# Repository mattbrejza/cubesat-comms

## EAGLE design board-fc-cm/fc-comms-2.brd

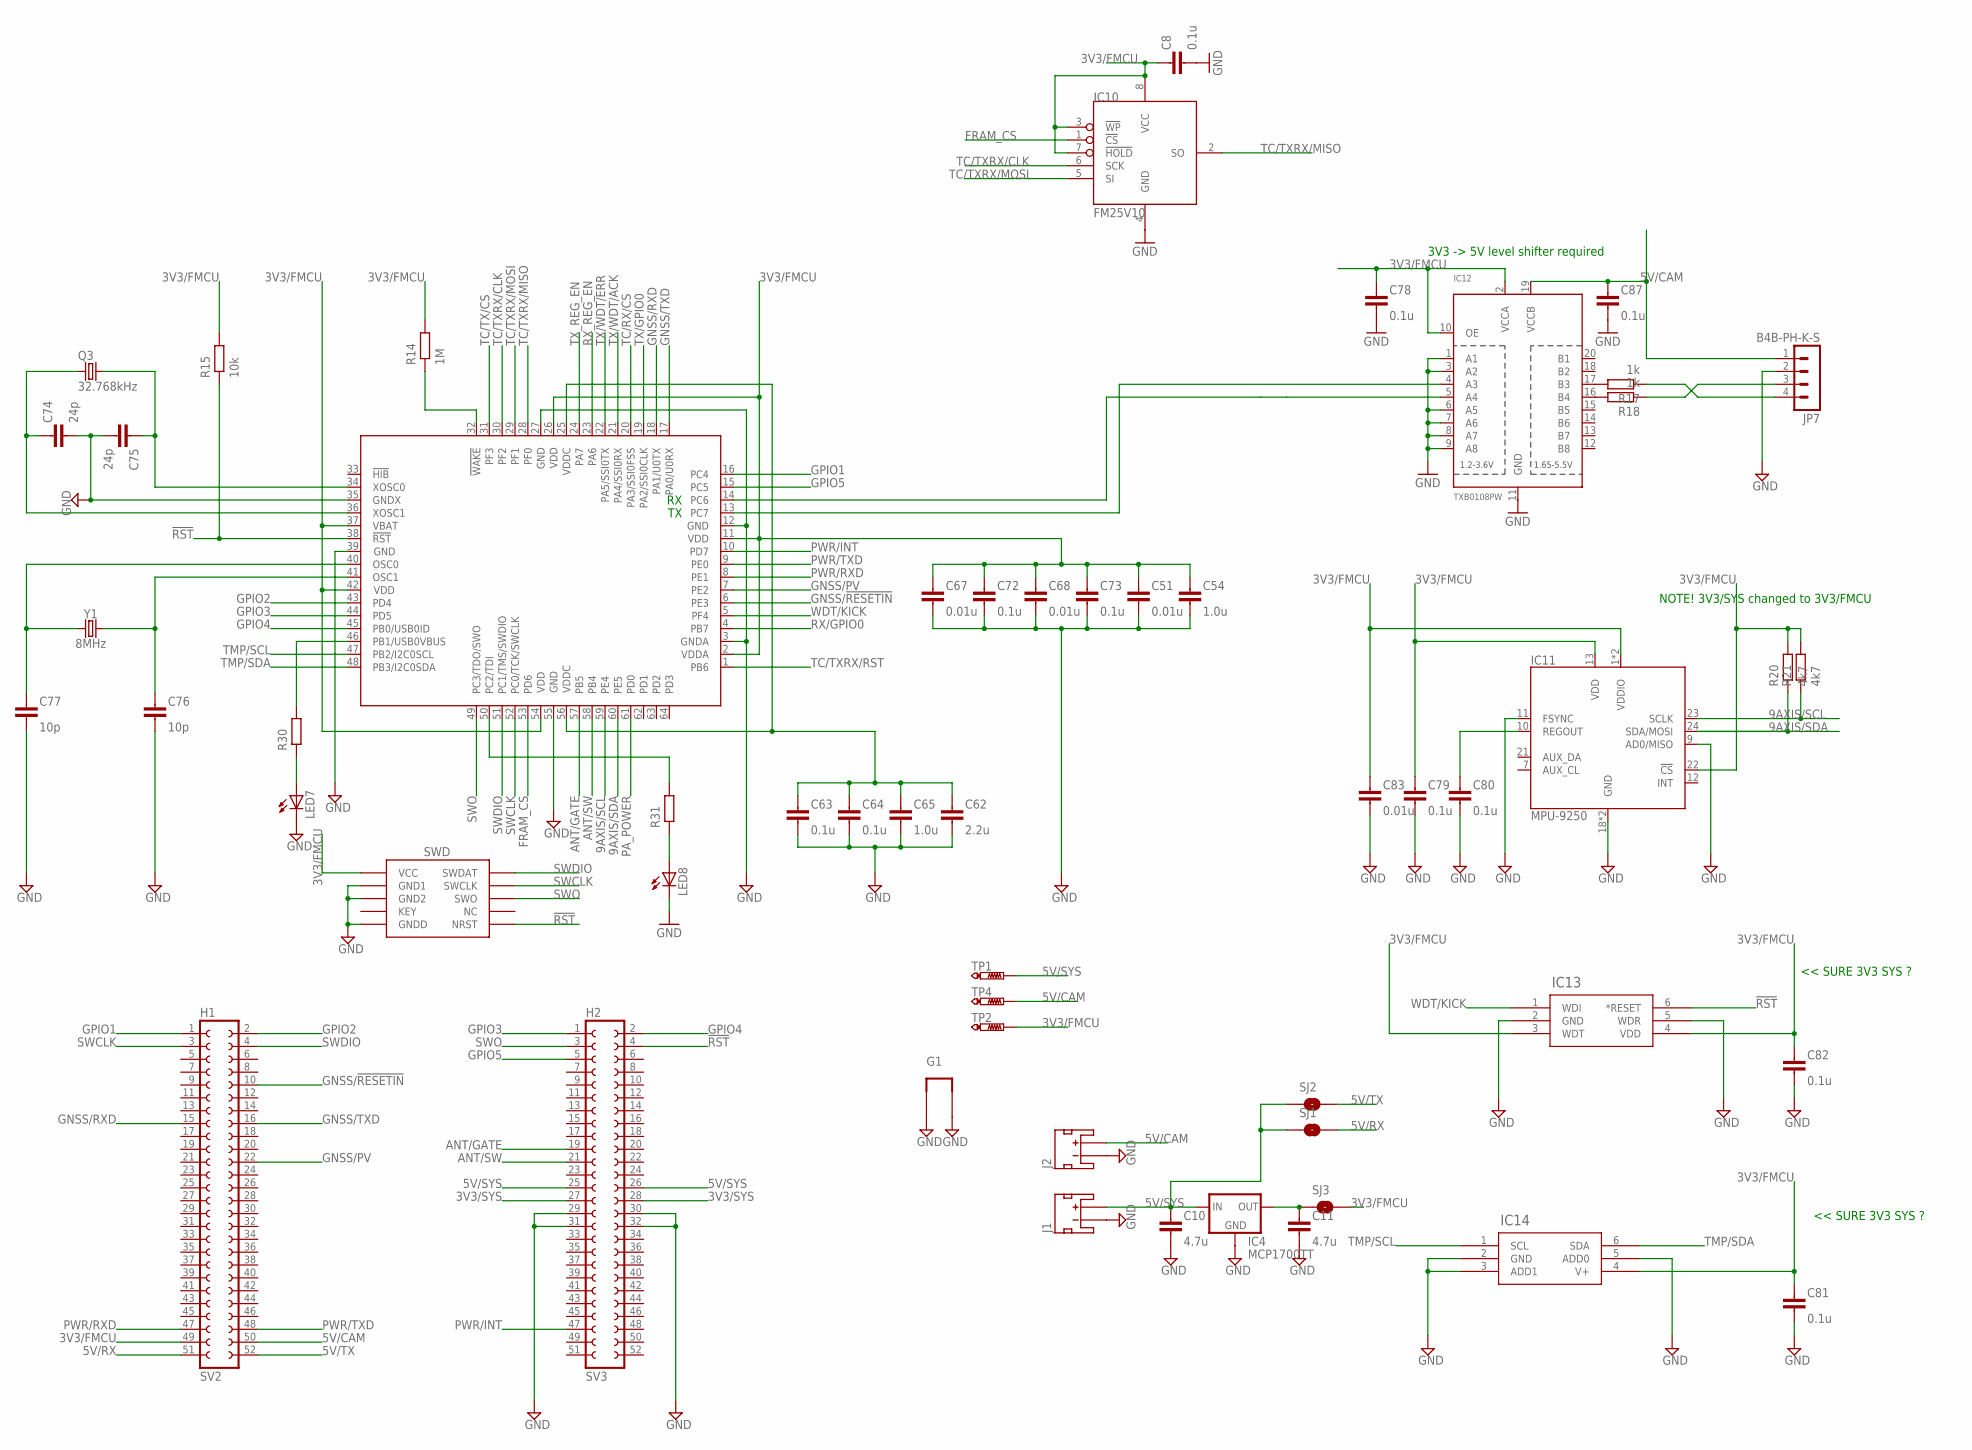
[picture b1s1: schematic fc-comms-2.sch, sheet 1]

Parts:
C8, C63, C64, C72, C73, C78, C79, C80, C81, C82, C87: 0.1u; C0603-N
C10, C11: 4.7u; C0603-N
C51, C67, C68, C83: 0.01u; C0603-N
C54, C65: 1.0u; C0603-N
C62: 2.2u; C0603-N
C74, C75: 24p; C0603-N
C76, C77: 10p; C0603-N
G1: GND-LOOPL; GND-LOOP-0.4
IC4: MCP1700TT; SOT23
IC9: TM4C123[7,G]XXPM; PM_S-PQFP-G64
IC10: FM25V10; SO-08M
IC11: MPU-9250; QFN-24/3MM
IC12: TXB0108PW; TSSOP20
IC13: TPS3813K33-EP_DBV_6; DBV6
IC14: TMP100-EP_DBV_6; DBV6
J1, J2: JST_2MM_MALE_TH; JST-2-TH
J3: SWD_SHROUD; SWD_PTH_SHROUD
JP7: B4B-PH-K-S
LED7, LED8: LEDCHIP-LED0603; CHIP-LED0603
Q3: 32.768kHz; RESONATOR_EPSON_FC_145; FARNELL 2101347
R14: 1M; R0603-N
R15: 10k; R0603-N
R17, R18: 1k; R0603-N
R20, R21: 4k7; R0603-N
R30, R31: RESISTOR0603-N; R0603-N
SJ1, SJ2, SJ3: JUMPER-PAD-2-NOYES_SILK; PAD-JUMPER-2-NO_YES_SILK
SV2: H1; FE26-2
SV3: H2; FE26-2
TP1, TP2, TP4: PTR1PAD1-13; P1-13
Y1: 8MHz; CRYSTAL-SMD-5X3.2-4PAD; FARNELL 2308726

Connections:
3V3/FMCU: C8.1, C51.1, C54.1, C67.1, C68.1, C72.1, C73.1, C78.1, C79.1, C81.1, C82.1, C83.1, IC9.2 (VDDA), IC9.11 (VDD), IC9.26 (VDD), IC9.37 (VBAT), IC9.42 (VDD), IC9.54 (VDD), IC10.3 (!WP), IC10.7 (!HOLD), IC10.8 (VCC), IC11.1 (VDDIO), IC11.8 (VDDIO), IC11.13 (VDD), IC11.22 (!CS), IC12.2 (VCCA), IC12.10 (OE), IC13.3 (WDT), IC13.4 (VDD), IC14.4 (V+), J3.1 (VCC), R14.2, R15.2, R20.2, R21.2, SJ3.2, SV2.49, TP2.TP; also elsewhere on the board
3V3/SYS: SV3.27, SV3.28
5V/CAM: C87.1, IC12.19 (VCCB), J2.1 (+), JP7.1, SV2.50, TP4.TP
5V/RX: SJ1.2, SV2.51; also elsewhere on the board
5V/SYS: C10.1, IC4.3 (IN), J1.1 (+), SJ1.1, SJ2.1, SV3.25, SV3.26, TP1.TP
5V/TX: SJ2.2, SV2.52; also elsewhere on the board
9AXIS/SCL: IC9.59 (PE4), IC11.23 (SCLK), R21.1
9AXIS/SDA: IC9.60 (PE5), IC11.24 (SDA/MOSI), R20.1
!RST: IC9.38 (!RST), IC13.6 (*RESET), J3.10 (NRST), R15.1, SV3.4
!WAKE: IC9.32 (!WAKE), R14.1
ANT/GATE: IC9.57 (PB5), SV3.19
ANT/SW: IC9.58 (PB4), SV3.21
CAM/RXD: IC9.13 (PC7), IC12.4 (A3)
CAM/TXD: IC9.14 (PC6), IC12.5 (A4)
FRAM_CS: IC9.53 (PD6), IC10.1 (!CS)
GND: C8.2, C10.2, C11.2, C51.2, C54.2, C62.2, C63.2, C64.2, C65.2, C67.2, C68.2, C72.2, C73.2, C74.2, C75.2, C76.2, C77.2, C78.2, C79.2, C80.2, C81.2, C82.2, C83.2, C87.2, G1.P$3 (1), G1.P$4 (2), IC4.1 (GND), IC9.3 (GNDA), IC9.12 (GND), IC9.27 (GND), IC9.35 (GNDX), IC9.39 (GND), IC9.55 (GND), IC10.4 (GND), IC11.9 (AD0/MISO), IC11.11 (FSYNC), IC11.18 (GND), IC11.20 (GND), IC12.1 (A1), IC12.3 (A2), IC12.6 (A5), IC12.7 (A6), IC12.8 (A7), IC12.9 (A8), IC12.11 (GND), IC13.2 (GND), IC13.5 (WDR), IC14.2 (GND), IC14.3 (ADD1), IC14.5 (ADD0), J1.2 (-), J2.2 (-), J3.3 (GND1), J3.5 (GND2), J3.9 (GNDD), JP7.2, LED7.C, LED8.C, SV3.29, SV3.30, SV3.31, SV3.32; also elsewhere on the board
GNSS/!RESETIN: IC9.6 (PE3), SV2.10
GNSS/PV: IC9.7 (PE2), SV2.22
GNSS/RXD: IC9.18 (PA1/U0TX), SV2.15
GNSS/TXD: IC9.17 (PA0/U0RX), SV2.16
GPIO1: IC9.16 (PC4), SV2.1
GPIO2: IC9.43 (PD4), SV2.2
GPIO3: IC9.44 (PD5), SV3.1
GPIO4: IC9.45 (PB0/USB0ID), SV3.2
GPIO5: IC9.15 (PC5), SV3.5
unnamed: C80.1, IC11.10 (REGOUT)
unnamed: C62.1, C63.1, C64.1, C65.1, IC9.25 (VDDC), IC9.56 (VDDC)
unnamed: C75.1, IC9.34 (XOSC0), Q3.P$2 (2)
unnamed: C77.1, IC9.40 (OSC0), Y1.1
unnamed: JP7.3, R18.1
unnamed: JP7.4, R17.1
unnamed: C76.1, IC9.41 (OSC1), Y1.3 (2)
unnamed: C74.1, IC9.36 (XOSC1), Q3.P$1 (1)
unnamed: LED7.A, R30.1
unnamed: LED8.A, R31.1
unnamed: IC9.50 (PC2/TDI), R31.2
unnamed: IC12.17 (B3), R17.2
unnamed: IC9.46 (PB1/USB0VBUS), R30.2
unnamed: IC12.16 (B4), R18.2
unnamed: C11.1, IC4.2 (OUT), SJ3.1
PA_POWER: IC9.61 (PD0); also elsewhere on the board
PWR/INT: IC9.10 (PD7), SV3.47
PWR/RXD: IC9.8 (PE1), SV2.47
PWR/TXD: IC9.9 (PE0), SV2.48
RX/GPIO0: IC9.4 (PB7); also elsewhere on the board
RX_REG_EN: IC9.23 (PA6); also elsewhere on the board
SWCLK: IC9.52 (PC0/TCK/SWCLK), J3.4 (SWCLK), SV2.3
SWDIO: IC9.51 (PC1/TMS/SWDIO), J3.2 (SWDAT), SV2.4
SWO: IC9.49 (PC3/TDO/SWO), J3.6 (SWO), SV3.3
TC/RX/CS: IC9.20 (PA3/SSI0FSS); also elsewhere on the board
TC/TX/CS: IC9.31 (PF3); also elsewhere on the board
TC/TXRX/CLK: IC9.30 (PF2), IC10.6 (SCK); also elsewhere on the board
TC/TXRX/MISO: IC9.28 (PF0), IC10.2 (SO); also elsewhere on the board
TC/TXRX/MOSI: IC9.29 (PF1), IC10.5 (SI); also elsewhere on the board
TC/TXRX/RST: IC9.1 (PB6); also elsewhere on the board
TMP/SCL: IC9.47 (PB2/I2C0SCL), IC14.1 (SCL); also elsewhere on the board
TMP/SDA: IC9.48 (PB3/I2C0SDA), IC14.6 (SDA); also elsewhere on the board
TX/GPIO0: IC9.19 (PA2/SSI0CLK); also elsewhere on the board
TX/WDT/ACK: IC9.21 (PA4/SSI0RX); also elsewhere on the board
TX/WDT/ERR: IC9.22 (PA5/SSI0TX); also elsewhere on the board
TX_REG_EN: IC9.24 (PA7); also elsewhere on the board
WDT/KICK: IC9.5 (PF4), IC13.1 (WDI)

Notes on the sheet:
3V3 -> 5V level shifter required
<< SURE 3V3 SYS ?
NOTE! 3V3/SYS changed to 3V3/FMCU

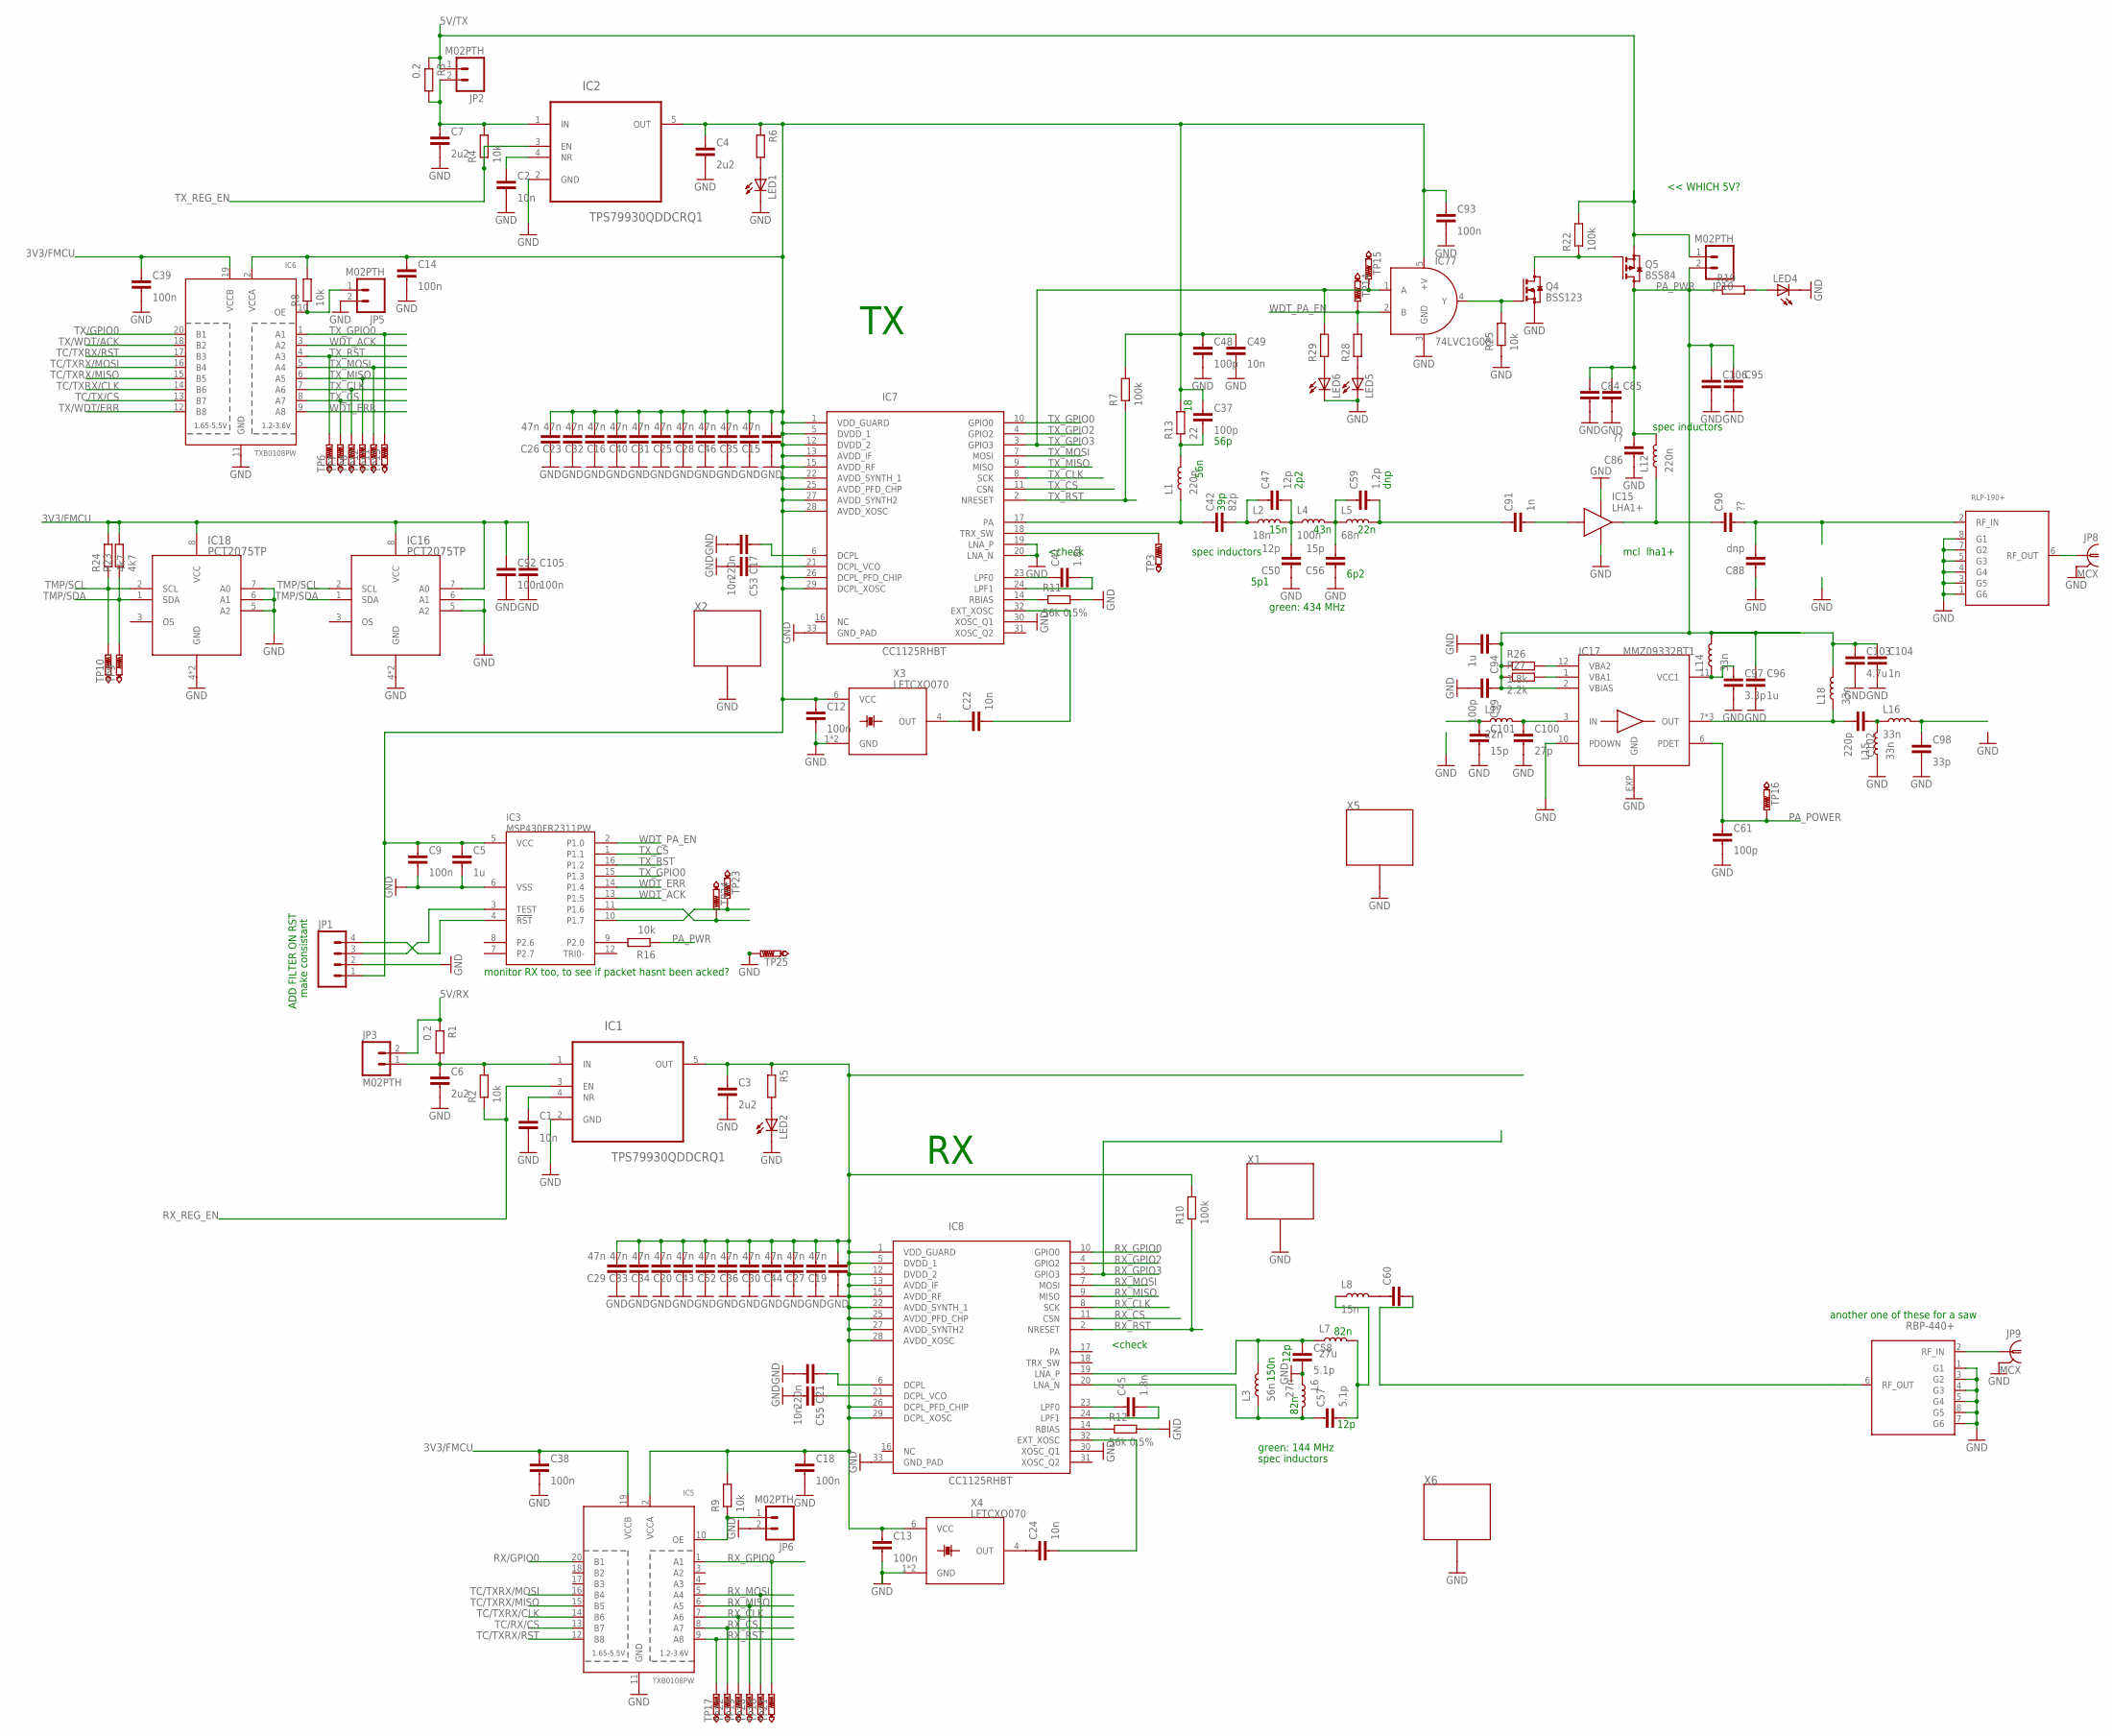
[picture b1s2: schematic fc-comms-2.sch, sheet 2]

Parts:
C1, C2, C22, C24, C49, C53, C55: 10n; C0603-N
C3, C4, C6, C7: 2u2; C0603-N
C5, C94, C96: 1u; C0603-N
C9, C12, C13, C14, C18, C38, C39, C92, C93, C105: 100n; C0603-N
C15, C16, C19, C20, C23, C25, C26, C27, C28, C29, C30, C31, C32, C33, C34, C35, C36, C40, C43, C44, C46, C52: 47n; C0603-N
C17, C21: 220n; C0603-N
C37, C48, C61, C99: 100p; C0603-N
C41, C45: 1.8n; C0603-N
C42: 82p; C0603-N
C47, C50: 12p; C0603-N
C56, C101: 15p; C0603-N
C57, C58: 5.1p; C0603-N
C59: 1.2p; C0603-N
C60: CAPACITOR0603-N; C0603-N
C84, C85, C95, C106: CAPACITOR0805-N; C0805-N
C86, C90: ??; C0603-N
C88: dnp; C0603-N
C91, C104: 1n; C0603-N
C97: 3.3p; C0603-N
C98: 33p; C0603-N
C100: 27p; C0603-N
C102: 220p; C0603-N
C103: 4.7u; C0603-N
FL2: SAW_FILTER_CS; PL-176
FL3: LPF_CS; PL-176
IC1, IC2: TPS79930QDDCRQ1; SOT95P280X110-5N
IC3: MSP430FR2311PW; SSOP16
IC5, IC6: TXB0108PW; TSSOP20
IC7, IC8: CC1125RHBT; QFN32_5X5
IC15: LHA1+; PA
IC16, IC18: PCT2075TP; HWSON8
IC17: MMZ09332BT1; QFN3X3-6
IC77: 74LVC1G08; SOT23-5
JP1: M04PTH; 1X04
JP2, JP3, JP5, JP6, JP10: M02PTH; 1X02
JP8, JP9: MCX; MCX-STRAIGHT
L1, L12: 220n; L0603-N
L2: 18n; L0603-N
L3: 56n; L0603-N
L4: 100n; L0603-N
L5: 68n; L0603-N
L6: 27n; L0603-N
L7: 27u; L0603-N
L8: 15n; L0603-N
L14, L15, L16, L18: 33n; L0603-N
L17: 22n; L0603-N
LED1, LED2, LED4, LED5, LED6: LEDCHIP-LED0603; CHIP-LED0603
Q4: BSS123; SOT23
Q5: BSS84; SOT23
R1, R3: 0.2; R0603-N
R2, R4, R8, R9, R16, R25: 10k; R0603-N
R5, R6, R19, R28, R29: RESISTOR0603-N; R0603-N
R7, R10, R22: 100k; R0603-N
R11, R12: 56k 0.5%; R0603-N
R13: 22; R0603-N
R23, R24: 4k7; R0603-N
R26: 1.8k; R0603-N
R27: 2.2k; R0603-N
TP3, TP6, TP7, TP8, TP9, TP10, TP11, TP12, TP13, TP14, TP15, TP16, TP17, TP18, TP19, TP20, TP21, TP22, TP23, TP24, TP25: PTR1B1,27; B1,27
X1, X2, X5, X6: SHIELD-26X26
X3, X4: LFTCXO070; 260-SERIES

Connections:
3V3/FMCU: C38.1, C39.1, C92.1, C105.1, IC5.19 (VCCB), IC6.19 (VCCB), IC16.7 (A0), IC16.8 (VCC), IC18.8 (VCC), R23.2, R24.2; also elsewhere on the board
5V/RX: JP3.2, R1.1; also elsewhere on the board
5V/TX: JP2.1, JP10.1, Q5.2 (S), R3.1, R22.2; also elsewhere on the board
EWFEWF: C6.1, IC1.1 (IN), JP3.1, R1.2, R2.2
GND: C1.2, C2.2, C3.2, C4.2, C5.2, C6.2, C7.2, C9.2, C12.2, C13.2, C14.2, C15.1, C16.1, C17.2, C18.2, C19.1, C20.1, C21.2, C23.1, C25.1, C26.1, C27.1, C28.1, C29.1, C30.1, C31.1, C32.1, C33.1, C34.1, C35.1, C36.1, C38.2, C39.2, C40.1, C43.1, C44.1, C46.1, C48.2, C49.2, C50.1, C52.1, C53.2, C55.2, C56.1, C58.2, C61.2, C84.2, C85.2, C86.1, C88.1, C92.2, C93.2, C94.2, C95.2, C96.2, C97.2, C98.2, C99.2, C100.2, C101.2, C103.2, C104.2, C105.2, C106.2, FL2.1 (G1), FL2.3 (G2), FL2.4 (G3), FL2.5 (G4), FL2.7 (G6), FL2.8 (G5), FL3.1 (G6), FL3.3 (G5), FL3.4 (G4), FL3.5 (G3), FL3.7 (G2), FL3.8 (G1), IC1.2 (GND), IC2.2 (GND), IC3.6 (VSS), IC5.11 (GND), IC6.11 (GND), IC7.19 (LNA_P), IC7.20 (LNA_N), IC7.30 (XOSC_Q1), IC7.33 (GND_PAD), IC8.30 (XOSC_Q1), IC8.33 (GND_PAD), IC15.GND1, IC15.GND2, IC16.4 (GND), IC16.5 (A2), IC16.6 (A1), IC16.EP (GND), IC17.10 (PDOWN), IC17.EXP (GND), IC18.4 (GND), IC18.5 (A2), IC18.6 (A1), IC18.7 (A0), IC18.EP (GND), IC77.3 (GND), JP1.2, JP5.2, JP6.2, JP8.P$2 (2), JP8.P$3 (2), JP8.P$4 (2), JP8.P$5 (2), JP9.P$2 (2), JP9.P$3 (2), JP9.P$4 (2), JP9.P$5 (2), L6.1, L15.1, LED1.C, LED2.C, LED4.C, LED5.C, LED6.C, Q4.2 (S), R11.2, R12.2, R25.1, TP25.TP, X1.G1, X1.G2, X1.G3, X1.G4, X1.G5, X1.G6, X1.G7, X1.G8, X1.G9, X1.G10, X1.G11, X1.G12, X1.G13, X1.G14, X1.G15, X1.G16, X1.G17, X1.G19, X1.G20, X1.G21, X2.G1, X2.G2, X2.G3, X2.G4, X2.G5, X2.G6, X2.G7, X2.G8, X2.G9, X2.G10, X2.G11, X2.G12, X2.G13, X2.G14, X2.G15, X2.G16, X2.G17, X2.G19, X2.G20, X2.G21, X3.1 (GND), X3.3 (GND), X4.1 (GND), X4.3 (GND), X5.G1, X5.G2, X5.G3, X5.G4, X5.G5, X5.G6, X5.G7, X5.G8, X5.G9, X5.G10, X5.G11, X5.G12, X5.G13, X5.G14, X5.G15, X5.G16, X5.G17, X5.G19, X5.G20, X5.G21, X6.G1, X6.G2, X6.G3, X6.G4, X6.G5, X6.G6, X6.G7, X6.G8, X6.G9, X6.G10, X6.G11, X6.G12, X6.G13, X6.G14, X6.G15, X6.G16, X6.G17, X6.G19, X6.G20, X6.G21; also elsewhere on the board
unnamed: IC3.9 (P2.0), R16.2
unnamed: C41.1, IC7.23 (LPF0)
unnamed: C41.2, IC7.24 (LPF1)
unnamed: LED5.A, R28.1
unnamed: C53.1, IC7.21 (DCPL_VCO)
unnamed: C42.1, IC7.17 (PA), L1.1
unnamed: IC7.14 (RBIAS), R11.1
unnamed: C22.2, IC7.32 (EXT_XOSC)
unnamed: C37.2, L1.2, R13.1
unnamed: C91.2, IC15.RF_IN
unnamed: C90.1, IC15.RF_OUT, L12.1
unnamed: C17.1, IC7.6 (DCPL)
unnamed: C42.2, C47.1, L2.1
unnamed: C47.2, C50.2, L2.2, L4.1
unnamed: C56.2, C59.1, L4.2, L5.1
unnamed: C59.2, C91.1, L5.2
unnamed: LED6.A, R29.1
unnamed: C88.2, C90.2, FL3.2 (RF_IN)
unnamed: FL3.6 (RF_OUT), JP8.P$1 (1)
unnamed: C45.1, IC8.23 (LPF0)
unnamed: C45.2, IC8.24 (LPF1)
unnamed: C55.1, IC8.21 (DCPL_VCO)
unnamed: IC8.14 (RBIAS), R12.1
unnamed: C24.2, IC8.32 (EXT_XOSC)
unnamed: LED4.A, R19.2
unnamed: IC7.18 (TRX_SW), TP3.TP
unnamed: C4.1, C5.1, C9.1, C12.1, C14.1, C15.2, C16.2, C23.2, C25.2, C26.2, C28.2, C31.2, C32.2, C35.2, C37.1, C40.2, C46.2, C48.1, C49.1, C93.1, IC2.5 (OUT), IC3.5 (VCC), IC6.2 (VCCA), IC7.1 (VDD_GUARD), IC7.5 (DVDD_1), IC7.12 (DVDD_2), IC7.13 (AVDD_IF), IC7.15 (AVDD_RF), IC7.22 (AVDD_SYNTH_1), IC7.25 (AVDD_PFD_CHP), IC7.26 (DCPL_PFD_CHIP), IC7.27 (AVDD_SYNTH2), IC7.28 (AVDD_XOSC), IC7.29 (DCPL_XOSC), IC77.5 (+V), JP1.1, R6.1, R7.2, R8.2, R13.2, X3.6 (VCC)
unnamed: LED1.A, R6.2
unnamed: C21.1, IC8.6 (DCPL)
unnamed: LED2.A, R5.2
unnamed: C58.1, IC8.19 (LNA_P), L3.2, L7.1
unnamed: C57.1, IC8.20 (LNA_N), L3.1, L6.2
unnamed: C3.1, C13.1, C18.1, C19.2, C20.2, C27.2, C29.2, C30.2, C33.2, C34.2, C36.2, C43.2, C44.2, C52.2, IC1.5 (OUT), IC5.2 (VCCA), IC8.1 (VDD_GUARD), IC8.5 (DVDD_1), IC8.12 (DVDD_2), IC8.13 (AVDD_IF), IC8.15 (AVDD_RF), IC8.22 (AVDD_SYNTH_1), IC8.25 (AVDD_PFD_CHP), IC8.26 (DCPL_PFD_CHIP), IC8.27 (AVDD_SYNTH2), IC8.28 (AVDD_XOSC), IC8.29 (DCPL_XOSC), R5.1, R9.2, R10.2, X4.6 (VCC)
unnamed: FL2.2 (RF_IN), JP9.P$1 (1)
unnamed: C60.2, FL2.6 (RF_OUT)
unnamed: C2.1, IC2.4 (NR)
unnamed: C1.1, IC1.4 (NR)
unnamed: Q4.3 (D), Q5.1 (G), R22.1
unnamed: C102.1, L15.2, L16.1
unnamed: C102.2, IC17.7 (OUT), IC17.8 (OUT), IC17.9 (OUT), L18.1
unnamed: C98.1, L16.2
unnamed: C97.1, IC17.11 (VCC1), L14.1
unnamed: IC17.12 (VBA2), R26.2
unnamed: IC17.1 (VBA1), R27.2
unnamed: C101.1, L17.1
unnamed: C100.1, IC17.3 (IN), L17.2
unnamed: C22.1, X3.4 (OUT)
unnamed: C24.1, X4.4 (OUT)
unnamed: IC3.3 (TEST), JP1.3
unnamed: IC3.4 (!RST), JP1.4
unnamed: IC3.11 (P1.6), TP24.TP
unnamed: IC3.10 (P1.7), TP23.TP
unnamed: C60.1, L8.2
unnamed: C57.2, L7.2, L8.1
unnamed: IC6.10 (OE), JP5.1, R8.1
unnamed: IC5.10 (OE), JP6.1, R9.1
unnamed: C7.1, IC2.1 (IN), JP2.2, R3.2, R4.2
unnamed: IC77.4 (Y), Q4.1 (G), R25.2
PA_POWER: C61.1, IC17.6 (PDET), TP16.TP; also elsewhere on the board
PA_PWR: C84.1, C85.1, C86.2, C94.1, C95.1, C96.1, C99.1, C103.1, C104.1, C106.1, IC17.2 (VBIAS), JP10.2, L12.2, L14.2, L18.2, Q5.3 (D), R16.1, R19.1, R26.1, R27.1
RX/GPIO0: IC5.20 (B1); also elsewhere on the board
RX_CLK: IC5.7 (A6), IC8.8 (SCK), TP19.TP
RX_CS: IC5.8 (A7), IC8.11 (CSN), TP22.TP
RX_GPIO0: IC5.1 (A1), IC8.10 (GPIO0), TP21.TP
RX_GPIO2: IC8.4 (GPIO2)
RX_GPIO3: IC8.3 (GPIO3)
RX_MISO: IC5.6 (A5), IC8.9 (MISO), TP20.TP
RX_MOSI: IC5.5 (A4), IC8.7 (MOSI), TP18.TP
RX_REG_EN: IC1.3 (EN), R2.1; also elsewhere on the board
RX_RST: IC5.9 (A8), IC8.2 (NRESET), R10.1, TP17.TP
TC/RX/CS: IC5.13 (B7); also elsewhere on the board
TC/TX/CS: IC6.13 (B7); also elsewhere on the board
TC/TXRX/CLK: IC5.14 (B6), IC6.14 (B6); also elsewhere on the board
TC/TXRX/MISO: IC5.15 (B5), IC6.15 (B5); also elsewhere on the board
TC/TXRX/MOSI: IC5.16 (B4), IC6.16 (B4); also elsewhere on the board
TC/TXRX/RST: IC5.12 (B8), IC6.17 (B3); also elsewhere on the board
TMP/SCL: IC16.2 (SCL), IC18.2 (SCL), R24.1, TP10.TP; also elsewhere on the board
TMP/SDA: IC16.1 (SDA), IC18.1 (SDA), R23.1, TP9.TP; also elsewhere on the board
TX/GPIO0: IC6.20 (B1); also elsewhere on the board
TX/WDT/ACK: IC6.18 (B2); also elsewhere on the board
TX/WDT/ERR: IC6.12 (B8); also elsewhere on the board
TX_CLK: IC6.7 (A6), IC7.8 (SCK), TP8.TP
TX_CS: IC3.1 (P1.1), IC6.8 (A7), IC7.11 (CSN), TP7.TP
TX_GPIO0: IC3.15 (P1.3), IC6.1 (A1), IC7.10 (GPIO0), TP13.TP
TX_GPIO2: IC7.4 (GPIO2)
TX_GPIO3: IC7.3 (GPIO3), IC77.1 (A), R29.2, TP15.TP
TX_MISO: IC6.6 (A5), IC7.9 (MISO), TP12.TP
TX_MOSI: IC6.5 (A4), IC7.7 (MOSI), TP11.TP
TX_REG_EN: IC2.3 (EN), R4.1; also elsewhere on the board
TX_RST: IC3.16 (P1.2), IC6.4 (A3), IC7.2 (NRESET), R7.1, TP6.TP
WDT_ACK: IC3.13 (P1.5), IC6.3 (A2)
WDT_ERR: IC3.14 (P1.4), IC6.9 (A8)
WDT_PA_EN: IC3.2 (P1.0), IC77.2 (B), R28.2, TP14.TP

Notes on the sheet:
spec inductors
<check
another one of these for a saw
mcl lha1+
make consistant
5p1
150n
82n
12p
green: 144 MHz
56n
56p
39p
2p2
6p2
15n
43n
22n
dnp
green: 434 MHz
monitor RX too, to see if packet hasnt been acked?
<< WHICH 5V?
ADD FILTER ON RST

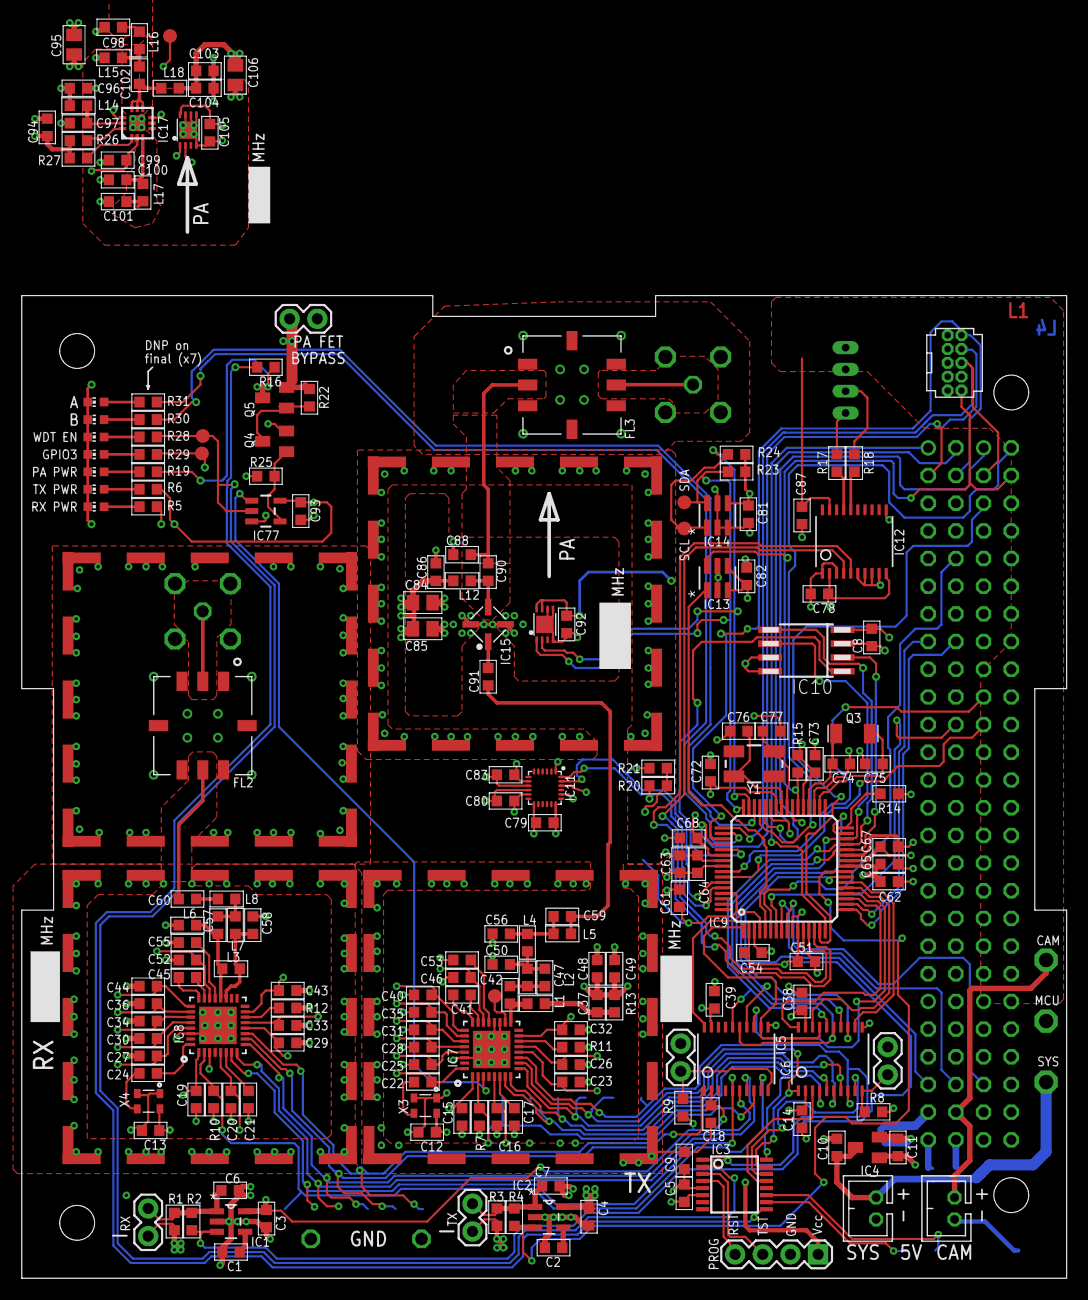
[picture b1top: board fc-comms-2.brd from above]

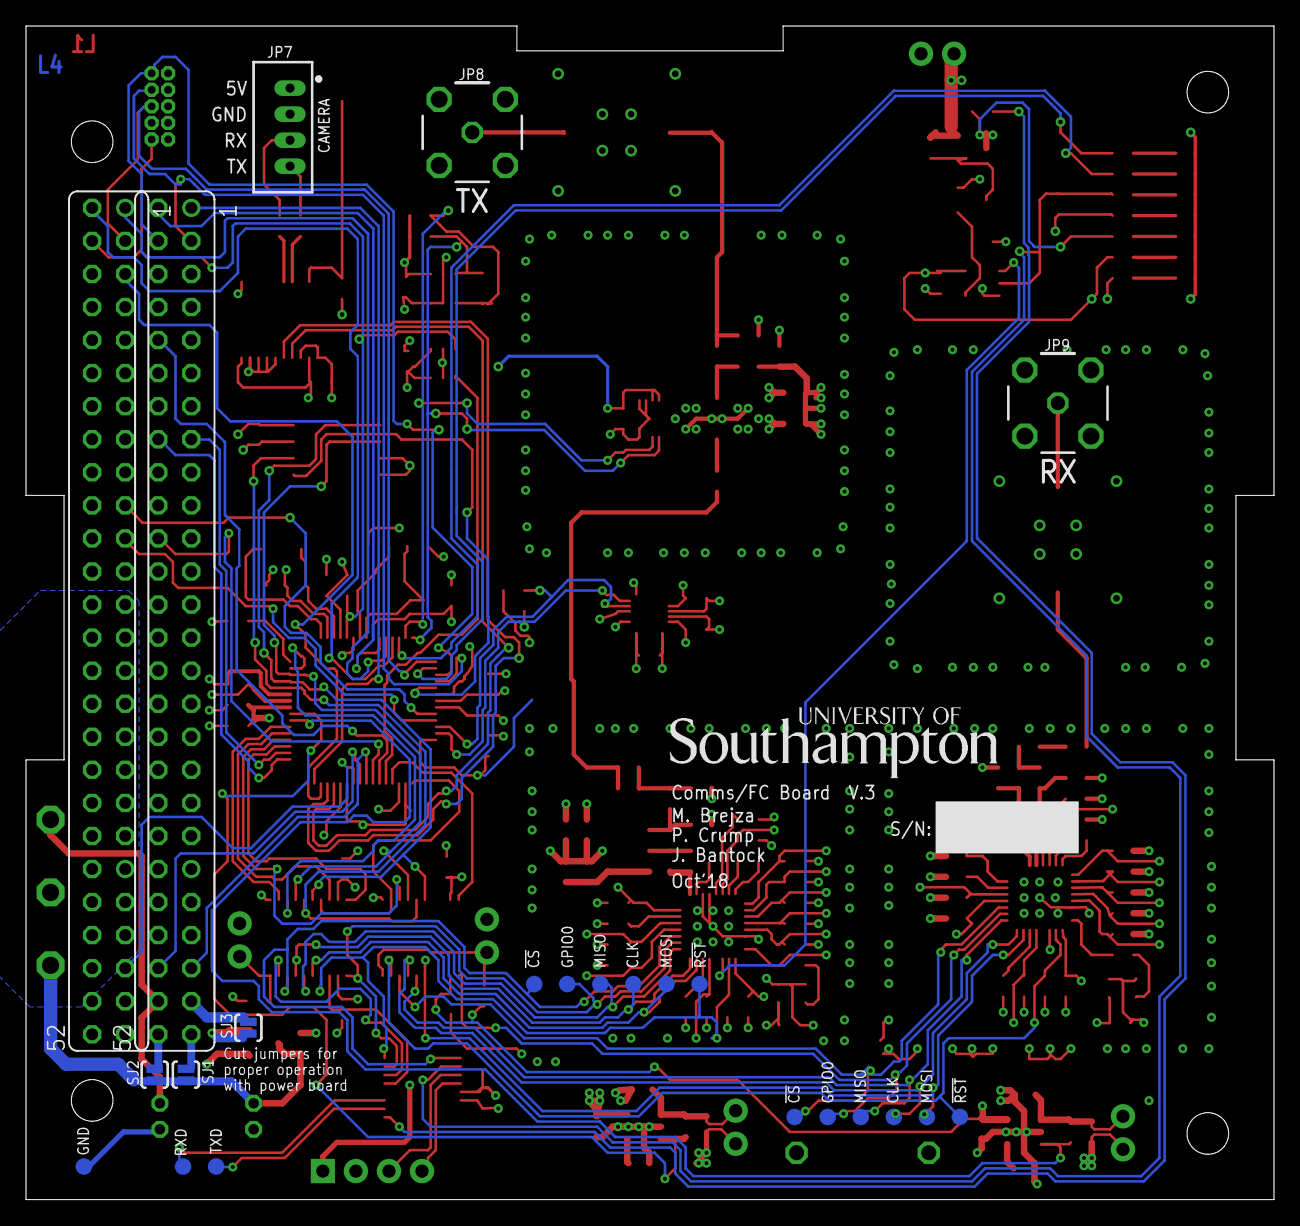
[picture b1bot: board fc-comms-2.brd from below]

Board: 4 copper layers, 95.9 x 90.2 mm, 228 parts (24 on the bottom side), 138 nets.

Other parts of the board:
U$1: OUTLINE
U$2: UOS_LOGO_SML

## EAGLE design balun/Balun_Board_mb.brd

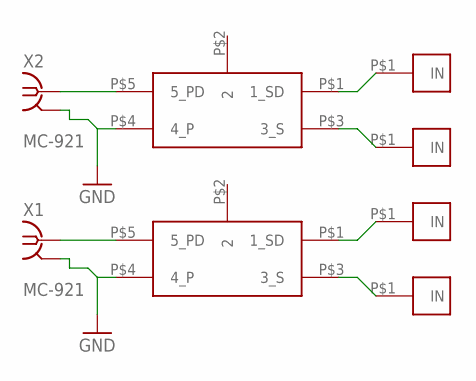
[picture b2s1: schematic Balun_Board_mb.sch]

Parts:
U$1, U$2: MABA-007159-000000
U$5, U$6, U$7, U$8: SMD-WIRE
X1, X2: MC-921

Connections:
GND: U$1.P$4 (4_P), U$2.P$4 (4_P), X1.2@1 (GND), X1.2@2 (GND), X2.2@1 (GND), X2.2@2 (GND)
unnamed: U$1.P$5 (5_PD), X2.1
unnamed: U$2.P$5 (5_PD), X1.1
unnamed: U$2.P$1 (1_SD), U$7.P$1
unnamed: U$2.P$3 (3_S), U$8.P$1
unnamed: U$1.P$1 (1_SD), U$5.P$1
unnamed: U$1.P$3 (3_S), U$6.P$1

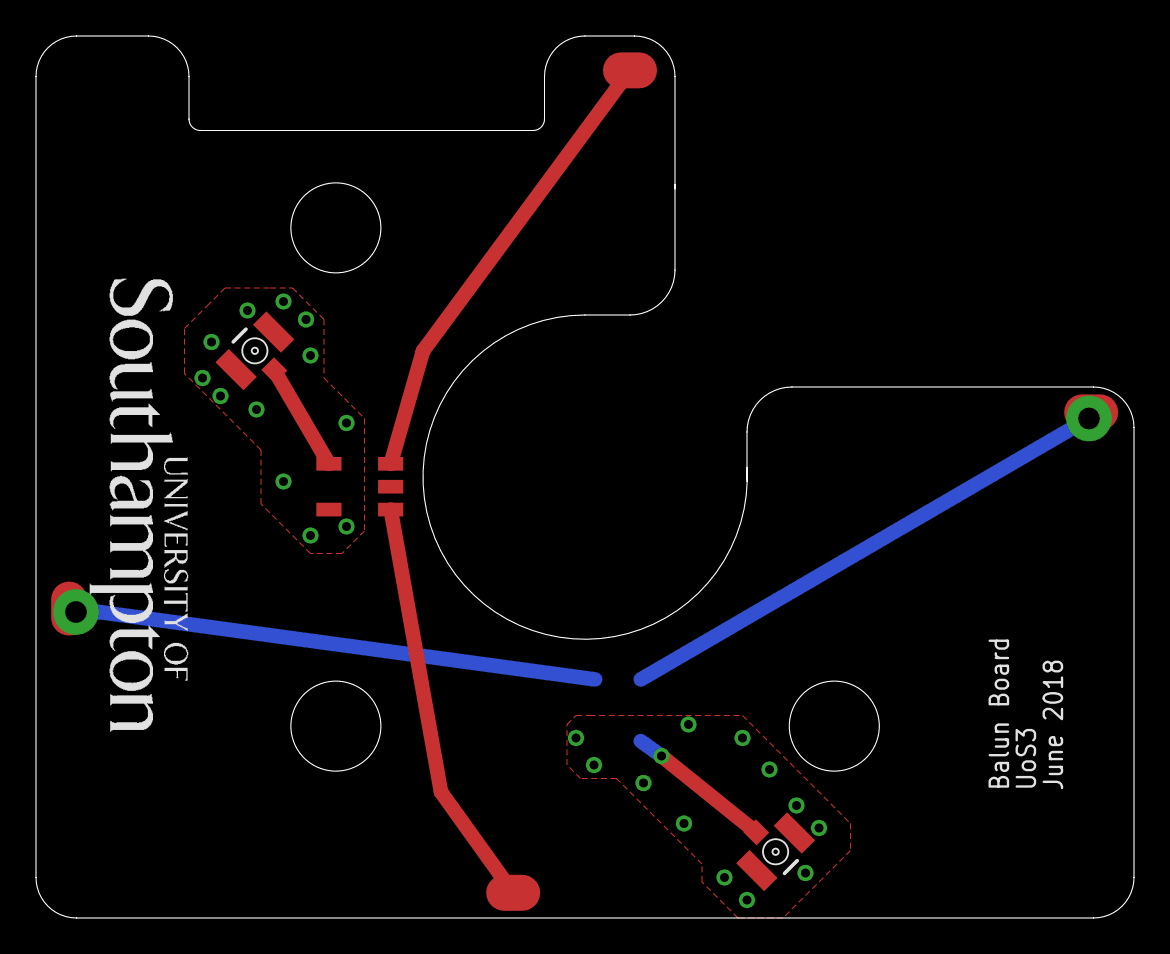
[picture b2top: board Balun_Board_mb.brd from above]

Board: 2 copper layers, 61.0 x 49.0 mm, 9 parts (1 on the bottom side), 7 nets.

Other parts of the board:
U$3: UOS_LOGO_SML

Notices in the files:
parts and their libraries:
SparkFun-Connectors: Licensing: Creative Commons ShareAlike 4.0 International - https://creativecommons.org/licenses/by-sa/4.0
